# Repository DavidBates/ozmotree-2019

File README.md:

# ozmotree-2019
NanoTree: A Christmas tree Inspired by Nanoleaf panels. Play Music. Watch Tree. https://ozmoapp.com

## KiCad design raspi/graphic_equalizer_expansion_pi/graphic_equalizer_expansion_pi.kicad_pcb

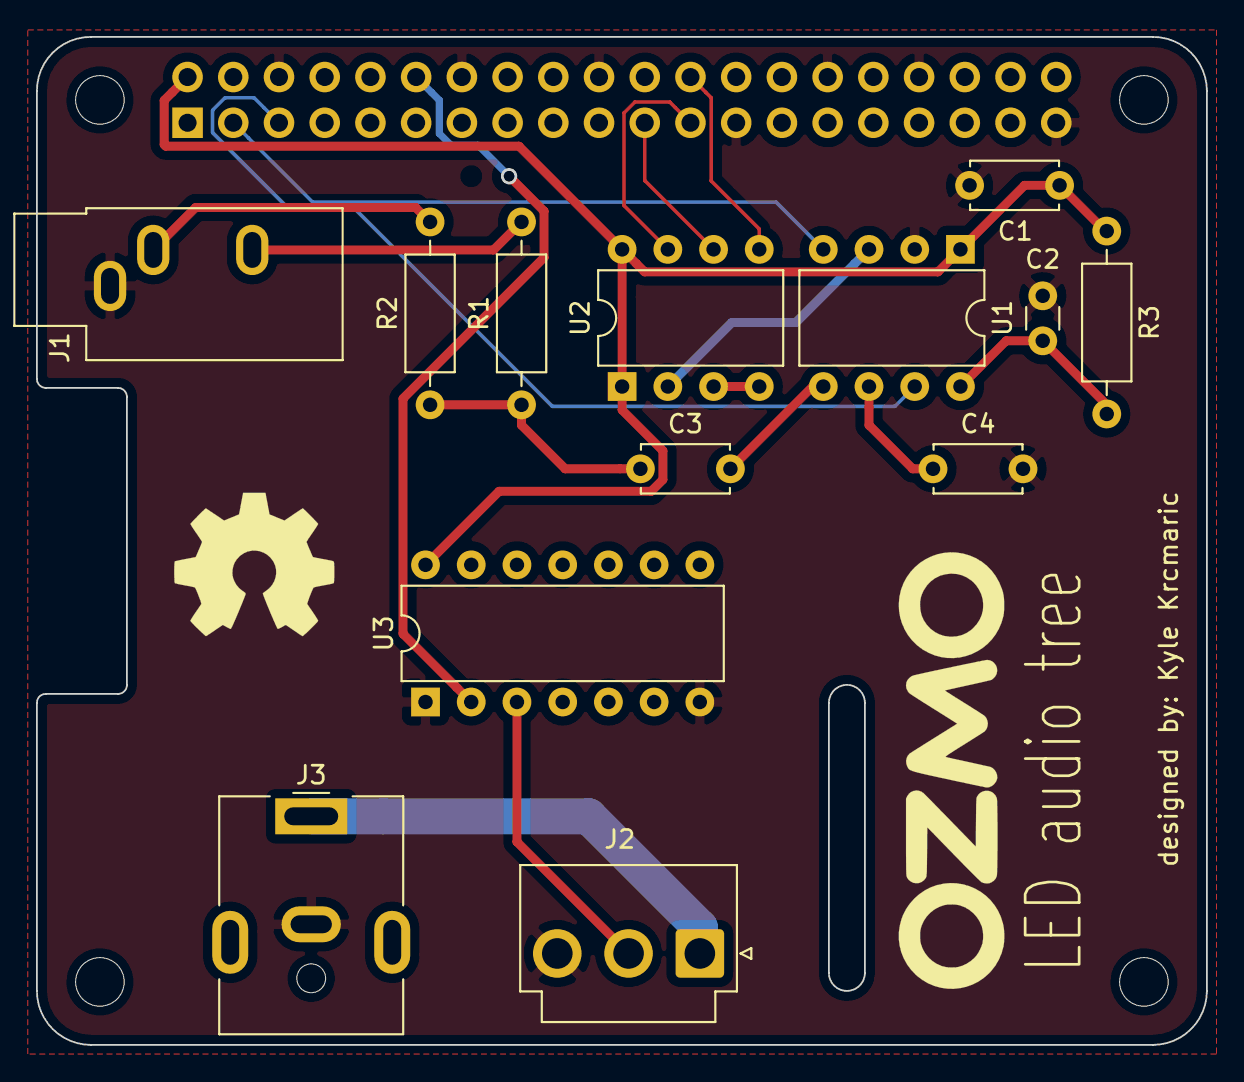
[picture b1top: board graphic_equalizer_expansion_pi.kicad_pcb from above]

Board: 2 copper layers, 65.0 x 56.0 mm, 18 parts (1 on the bottom side), 19 nets.

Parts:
C1, C3, C4: 0.1u; C_Disc_D4.7mm_W2.5mm_P5.00mm
C2: 33p; C_Disc_D3.0mm_W1.6mm_P2.50mm
J1: AudioJack3; Jack_3.5mm_CUI_SJ1-3533NG_Horizontal
J2: Conn_01x03; JST_VH_B3P-VH_1x03_P3.96mm_Vertical
J3: Barrel_Jack; BarrelJack_CUI_PJ-063AH_Horizontal
MK1, MK2, MK3, MK4: M2.5; MountingHole_2.7mm_M2.5
P1: Conn_02x20_Odd_Even; PinSocket_2x20_P2.54mm_Vertical
R1, R2: 22K; R_Axial_DIN0207_L6.3mm_D2.5mm_P10.16mm_Horizontal
R3: 200K; R_Axial_DIN0207_L6.3mm_D2.5mm_P10.16mm_Horizontal
U1: MSGEQ7; DIP-8_W7.62mm
U2: MCP3001; DIP-8_W7.62mm
U3: SN74AHCT125N; DIP-14_W7.62mm

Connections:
+3V3: P1.1, P1.17
+5V: C1.2, P1.2, P1.4, R3.1, U1.1, U2.1, U2.8, U3.14
ADC_CLK: P1.23, U2.7
AUDIO_DATA: P1.21, U2.6
CHIP_SELECT: P1.24, U2.5
GND: C1.1, C2.2, C4.2, J1.S, J2.3, J3.2, P1.6, P1.9, P1.14, P1.20, P1.25, P1.30, P1.34, P1.39, U1.2, U3.1, U3.7
NEO_DATA: P1.12, U3.2
unnamed: C2.1, R3.2, U1.8
unnamed: C3.1, R1.1, R2.1
unnamed: C3.2, U1.5
unnamed: C4.1, U1.6
unnamed: J1.R, R1.2
unnamed: J1.T, R2.2
unnamed: J2.1, J3.1
unnamed: J2.2, U3.3
unnamed: U1.3, U2.2
unnamed: U2.3, U2.4
RESET: P1.5, U1.7
STROBE: P1.3, U1.4

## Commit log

2019-11-13 Add raspberry pi expansion board schematic PDF
2019-11-23 Adding tree design files
2019-11-25 Add python script to talk to ADC and neopixels
2019-11-28 untested, blind-coded script for controlling tree lighting
2019-12-12 Add PCB design files
